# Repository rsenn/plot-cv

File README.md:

# EAGLE viewer (name pending — see below)

A browser-based viewer/editor for EAGLE CAD `.brd`/`.sch`/`.lbr` XML files: parses
the EAGLE XML DOM, renders schematics and boards to SVG, and drives a CAM pipeline
(Gerber export, G-code conversion) for board files. Includes a project/file chooser
for browsing available EAGLE projects on the backend.

Currently named "EAGLE renderer" (`index.html` `<title>`) — that name undersells the
CAM/editing features and needs to change. Candidates:

- **Eyrie** / **Aerie** — a bird of prey's nest; keeps the EAGLE association as a real
  English word instead of the acronym.
- **TalonView**
- **Wingspan**
- **BoardScope**
- **SchemaHawk**
- **CircuitEye**
- **GerberEye**

## Architecture

- **`index.html` + `main.js`** — the browser frontend. Preact-based UI (custom bundled
  `lib/preact.js`, not the npm package) that renders the SVG document, project/file
  chooser, layer controls, and CAM tooling. Talks to the backend over `fetch`/XHR
  (`commands.js`) and WebSockets (serial bridge, live update pushes).
- **`server.js`** — the current backend: a Node/Express server exposing the project's
  file listing, EAGLE file load/save, Gerber/G-code conversion, serial-port bridging
  (websocket), and static asset serving that `main.js` depends on.
- **`upload-server.js`** — an experimental, partial replacement backend built directly
  on qjs-net's low-level `createServer()` (QuickJS), meant to eventually take over from
  `server.js`. Not yet endpoint-compatible with `main.js`/`commands.js` — see `TODO.md`.

## OpenCV/ImGui Viewer

Simple OpenCV viewer using Dear ImGui interface.

Only testd on MacOSX.

# Dependency

- OpenCV>3.0
- SDL2
- Dear ImGui

# How to build

```
git clone https://github.com/ocornut/imgui.git
mkdir build
cd build
export OpenCV_DIR=OPENCV_INSTALL_PATH
cmake ..
make
```

# Root Script Index

Every `*.js` file directly in the repo root that has its own `main(...)` entry point
(`grep -lE '\bmain\s*\(' *.js`), sorted by line count as a rough proxy for
importance/complexity — substantial standalone tools/servers/apps at the top,
small one-off `test-*.js` smoke-test scripts at the bottom.

| Script | Lines | Description |
|---|---:|---|
| `tradeview.js` | 2166 | GLFW/nanovg GUI viewer for a crypto trading bot's SQLite database — renders candlestick charts, signals, trade brackets, and equity curve |
| `resolve-imports2.js` | 1730 | recursively resolves and concatenates a JS module's ES6 import graph into a single bundled `.es` output file |
| `eagle-shell.js` | 1657 | interactive REPL shell for loading EAGLE CAD schematic/board XML projects and manipulating parts, layers, and renderers, with gerber/gcode/SVG tools |
| `ast-shell.js` | 1655 | interactive REPL shell for compiling C/C++ sources to clang AST-dump JSON and exploring types/functions/structs, with FFI class generation |
| `resolve-imports.js` | 1397 | CLI ES-module tool that lexes JS files' import/export statements and can strip/rewrite imports, print dependency trees, or write reports |
| `upload-server.js` | 1328 | qjs-net HTTPS/WebSocket file-upload server — accepts multipart uploads, lists/serves them with directory browsing and thumbnails, plus a REPL |
| `fire.js` | 1019 | browser demo — renders a classic "Doom fire" pixel-propagation effect on canvas, seeded by mouse/touch input via a requestAnimationFrame loop |
| `debugger-server.js` | 1014 | qjs-lws WebSocket server that spawns and manages a QuickJS debugger session, relaying debugger protocol messages to connected clients |
| `server.js` | 947 | Express.js backend for the EAGLE/gerber CAD viewer web app — routes for gerber/gcode conversion, VFS/file access, serial ports, project save/config |
| `test-video.js` | 786 | interactive OpenCV.js video-processing test harness — reads a video/camera source through a Canny/contour/Hough pipeline with MIDI input |
| `test-opencv.js` | 723 | interactive OpenCV.js/GLFW smoke-test app — builds a live image-processing pipeline (threshold, Hough, skeleton) with mouse/keyboard tuning |
| `svg-crop-pad.js` | 682 | CLI that loads SVG files, computes/prints their bounding box, and rewrites the `viewBox`/width/height to crop or pad the drawing |
| `webakeit-telegram.js` | 633 | site-specific variant of the Telegram-export-to-blog converter, tailored to build `blog.html` for the webakeit bakery site |
| `dump-structs.js` | 592 | runs C/C++ source through `clang -ast-dump`, analyzes typedef'd structs/function prototypes, and generates JS ArrayBuffer struct/FFI bindings |
| `telegram-to-blog.js` | 569 | converts a Telegram Desktop HTML chat export into a self-contained static HTML blog page, copying/rotating referenced photos |
| `dump-ast.js` | 496 | runs `clang -ast-dump=json` on a C source file, then walks the AST to locate structs, printf-family calls, and format-string argument ranges |
| `test-xml.js` | 472 | reads a Sublime Text `.tmTheme` XML color scheme, extracts its color palette, applies a chosen transform, and writes back a modified theme |
| `list-exports.js` | 458 | lexes JS/BNF-family source files to find `import`/`export` statements and prints an `import { ... } from 'file'` summary line per file |
| `object_detection.js` | 451 | OpenCV.js DNN sample — loads a Caffe/TensorFlow/Darknet/ONNX model, runs object detection on video/camera/image with NMS |
| `create-tamper.js` | 437 | parses a set of JS module files, inlines/resolves their imports/exports recursively, and emits a bundled Tampermonkey userscript |
| `adsb-server.js` | 430 | qjs-lws WebSocket/TCP server that watches ADS-B state-dump files (inotify) and serves live aircraft-state updates to connected clients |
| `google-contacts.js` | 415 | QuickJS CLI that OAuth2-authenticates with Google People API, fetches all contacts, and prints/dumps them sorted by last-modified time |
| `photo_categorizer.js` | 412 | runs YOLOv8 (ONNX via OpenCV dnn) on all images in a folder, sorts each into a category subfolder based on detected objects |
| `test-rpc.js` | 410 | RPC/WebSocket test harness — starts an RPC client or server (file-serving, upload, proxy handlers) and drops into an interactive REPL |
| `test-image.js` | 404 | interactive OpenCV image viewer/pipeline tool — opens a window with mouse callback, runs images through an `ImagePipeline`, exports SVG/JSON |
| `eagle-server.js` | 376 | WS/HTTP backend server (custom `net` module) — serves static files plus `/config` and `/files` routes over TLS/WS, with a live-control REPL |
| `test-imgui.js` | 345 | interactive GLFW+nanovg+ImGui demo window exercising most ImGui widget bindings alongside a simple nanovg-drawn diamond shape |
| `ffi.js` | 327 | low-level libc FFI test/demo — dlopen/dlsym libc, calls malloc/strlen/strdup, then opens a raw TCP socket via syscalls and sends a manual HTTP GET |
| `test.js` | 314 | exercises OpenCV geometry/contour bindings plus edge/contour detection (Canny, findContours) on an input image, walking the contour hierarchy |
| `test-ffi.js` | 308 | exercises the custom `ffi` QuickJS module — dlopen/dlsym/call on libc functions, a bundled test.so, and inline x86-64 machine code |
| `test-parsetmpl.js` | 308 | tests `ECMAScriptParser`'s handling of tagged template literals, extracting tagged-template call nodes and running a JSX-string tokenizer |
| `list-proxies.js` | 303 | Node.js CLI that scrapes free proxy lists from multiple sources for given country codes, pings each proxy, and writes sorted results |
| `test-quickjs.js` | 299 | smoke test/exercise of the `opencv` module bindings (CV_* constants, Contour push/index/fitLine/fitEllipse), largely mirroring test-cv.js |
| `svg-box.js` | 292 | generates a laser-cutter SVG template for a box (lid/bottom/front/back/sides) with measurement annotations from CLI dimension args |
| `yolo.js` | 287 | real YOLOv3 object-detection CLI using OpenCV `dnn` — runs inference on image/video/webcam, draws bounding boxes+labels, saves JSON detections |
| `test-ecmascript2.js` | 284 | near-duplicate of test-ecmascript.js — parses a JS file, writes AST JSON and reprinted source, reporting parse success/failure |
| `test-eagle.js` | 278 | exercises the `lib/eagle.js` EAGLE CAD project API — loads a board/schematic project, normalizes pads, aligns elements to grid, saves documents |
| `test-mmap.js` | 275 | binary-patching tool — mmaps a target executable, scans it for byte patterns (license-check signatures), and writes out a patched copy |
| `blackbody.js` | 263 | looks up an RGB gamma correction triple for a given color temperature in a blackbody color table and prints an mpv/ffmpeg filter string |
| `doc-scanner.js` | 256 | OpenCV document-scanner script — finds the largest 4-point contour in an image, warps/crops it to a fixed page size, displays/writes results |
| `list-exports2.js` | 256 | CLI that parses a JS file, extracts its exported/imported identifiers, and prints/writes a synthesized `import {...} from './file'` statement |
| `test-nanovg.js` | 251 | interactive GLFW+nanovg+ImGui+OpenCV demo — draws a background image, animates transformed shapes with nanovg, renders an ImGui panel |
| `clang-list.js` | 249 | CLI that runs/loads a clang AST dump for given source files (caching), flattens it, and prints a table of named declarations |
| `test-ecmascript.js` | 248 | CLI that parses a JS file (or stdin) with the custom `ECMAScriptParser`, dumps the AST to JSON, and reports imports/requires/templates |
| `test-kolorwheel.js` | 238 | generates/prints color palettes/gradients using `KolorWheel`/`HSLA`/`RGBA`, mapping Eagle CAD layer names to a randomized palette |
| `test-cv.js` | 230 | smoke test of the `opencv` module bindings — Rect/Point/Size/Line/Mat/Contour constructors, Mat pixel get/set, iterators |
| `get-msys-packages.js` | 227 | downloads MSYS2/MinGW package DB files, resolves package/dependency args against them, and generates a script to curl+extract matches |
| `svgtransform.js` | 222 | CLI that reads an SVG/XML file, applies accumulated `transform` attributes as matrices to child elements, and rewrites their coordinates |
| `test-tmtheme.js` | 221 | converts TextMate `.tmLanguage`/`.tmTheme` plist XML files to/from a JS object model, extracts scope names, and rewrites the plist file |
| `cv-shell.js` | 213 | interactive OpenCV/CV REPL shell wiring up image/video helpers, history, and globals for live experimentation with `qjs-opencv` |
| `svg-scale.js` | 213 | CLI that reads SVG file(s), inlines CSS classes into attributes, reformats path data, and resizes the SVG to a given size, rewriting in place |
| `gerber2gcode.js` | 208 | CLI that groups Gerber/drill files by board, parses them, builds a `pcb2gcode` command line, runs it, and post-processes the resulting SVG |
| `scan.js` | 197 | OpenCV-based A4 document scanner CLI: detects the page quadrilateral, perspective-warps/thresholds it, and writes contour JSON plus PNG outputs |
| `check-discogs.js` | 196 | fetches Discogs seller order pages via spawned `curl` for given order IDs and prints/collects order info (mostly a stub) |
| `esparse.js` | 195 | CLI that parses a JS source file with the custom `ECMAScriptParser`, adds comments to the AST, and writes it as JSON to an output file |
| `compile_commands.js` | 194 | loads a `compile_commands.json`, builds `CompileCommand` objects and dependency maps, and parses CMake `link.txt` files |
| `test-ecmascript3.js` | 193 | CLI driver for the project's custom ECMAScript parser: parses input file(s), pretty-prints the AST back to `.es`/`.ast.json`, scans imports |
| `test-bjson.js` | 177 | standalone test of a custom `bjson.so` binary-JSON module — round-trips a BJSON file to JSON, with zlib/XML FFI helpers defined but unused in main() |
| `test-ini.js` | 175 | parses a `.desktop`/INI-style file with a custom INI grammar and converts it into an icon entry or reshuffles sections, rewriting the file |
| `test-umat.js` | 175 | OpenCV demo dumping Mat type constants, then running Canny/Hough/contour analysis on a schematic image and displaying results |
| `xml2js.js` | 172 | CLI that reads an XML file (e.g. EAGLE board file), converts it to a `Tree`, strips empty/wrapper nodes, and writes cleaned JSON/BJSON/XML |
| `test-filesystem.js` | 164 | TinyTest-based unit test suite exercising the `filesystem` module's buffer/file/dir API against a temp directory |
| `test-debuggerprotocol.js` | 159 | CLI that opens a raw TCP socket to a QuickJS debugger endpoint (client or server mode) and drives the `DebuggerProtocol` class |
| `adsb-client.js` | 157 | polls the OpenSky Network REST API for ADS-B aircraft state vectors every 10s and appends the JSON responses to rotating log files |
| `test-imread.js` | 156 | OpenCV demo that loads a bitmap-font image, segments it into a character grid, renders each glyph as ASCII art in a GUI window |
| `test-membrane.js` | 153 | parses an EAGLE `.brd` XML file, exercising the `deep`/`ImmutablePath`/`XMLIterator`/`ImmutableXPath` membrane-style path-mapping APIs |
| `sky_detect.js` | 149 | OpenCV CLI tool that loads an image, builds an HSV-based sky mask, finds the largest contour, and writes mask/contour PNG outputs |
| `test-midi.js` | 149 | standalone smoke test connecting to a TCP MIDI stream, decoding incoming bytes into MIDI events and logging them |
| `search-engine.js` | 147 | async scraper that queries several search-engine URL templates, parses HTML with the custom DOM parser, and extracts `src`/`href` links |
| `test-cparse.js` | 144 | exercises the custom `cpp`/`cparse` C preprocessor and parser libraries by preprocessing/parsing a hardcoded quickjs C source file |
| `test-minnet.js` | 143 | smoke test/demo of the `net` (minnet) module's `createServer`/`client`/`fetch` APIs, selectable via CLI arg |
| `convert-imports.js` | 142 | CLI that parses a JS file, finds `require()`/`import` nodes via `deep.select`, and converts between `import` and `require` styles |
| `test-glfw.js` | 138 | opens a GLFW/OpenGL window, loads image(s) via `opencv.imread`, uploads them as GL textures, and animates a color-cycling textured quad |
| `midi-tcp.js` | 130 | connects to a TCP MIDI stream, parses incoming MIDI events with `MIDIStream`/`MIDIEvent`, and reads raw stdin bytes (Ctrl-D to quit) |
| `eagle2gerber.js` | 129 | CLI tool that invokes the Eagle CAD binary to export Gerber/Excellon layers from `.brd` files, then zips the generated output folder |
| `test-features2d.js` | 119 | iterates OpenCV's Feature2D detector/descriptor classes (ORB, AKAZE, SURF, MSER, etc.), computes keypoints, and displays them |
| `test-fft.js` | 109 | loads a WAV file via `libsndfile` (raw FFI), runs an FFT (`lib/dsp/fft.js`) on a windowed segment, and prints the dominant frequency bin(s) |
| `yt-playlist.js` | 98 | runs `yt-dlp` as a subprocess to fetch JSON metadata for a YouTube playlist URL, then writes the collected results to `out.json` |
| `test-attributes.js` | 97 | reads XML files, collects the set of attribute names used per tag across all elements, and prints which attribute names hold numeric values |
| `bs.to-serie.js` | 96 | scrapes a "Burning Series" streaming site — reads show URLs from a text file and extracts metadata (title, actors, genres, years) into an array |
| `test-net.js` | 93 | smoke-test of the `net.so` module's `fetch()` — performs a GET request to google.com with a custom User-Agent |
| `xml2react.js` | 93 | reads XML (from a file or stdin) and converts it into `h(...)`-style React/hyperscript-like JS source code, printed to stdout |
| `read-deps.js` | 90 | runs `g++ -MM` to compute header dependencies for C/C++ sources, writes `deps.mk`, and cross-checks against a manual `#include` scan |
| `test-proxy.js` | 89 | reads an Eagle `.brd` XML file, wraps it in a lazy `Proxy`-based node/nodelist tree, and walks it with `deep.select` to find named parts |
| `extract-structs.js` | 87 | lexes a C source file with `CLexer` and prints out top-level `struct`/`typedef` declarations found at column 1 |
| `make-bitmap.js` | 87 | interactive OpenCV pipeline tool that loads an image, applies grayscale + adjustable threshold via a trackbar, and displays the result |
| `test-coverage.js` | 86 | reads a V8 coverage JSON report, matches script URLs against a regex, and computes/extracts used vs. unused source code ranges |
| `count-neighbours.js` | 85 | loads an image, thresholds/skeletonizes it with OpenCV, computes pixel-neighborhood/skeleton tracing, and drops into an interactive REPL |
| `test-inspect.js` | 82 | smoke-tests the QuickJS `inspect`/`Console` utilities by building an object with exotic values and printing it with various inspect options |
| `test-jsjs.js` | 82 | parses JS source file(s) with the custom `ECMAScriptParser`, re-prints the AST via `Printer` to a `.es` output file |
| `video-image-similarity.js` | 82 | opens a video file in an OpenCV `Window`, computes frame-to-frame MSE similarity in grayscale, and lets the user save frames as PNG |
| `ftrace.js` | 81 | parses an strace log file, reconstructs resumed syscalls, and writes lists of referenced filenames and functions that touched files |
| `test-childprocess.js` | 81 | spawns `ls -la` via `child_process.spawn`, sends SIGSTOP/SIGCONT to it, and streams its stdout via a custom `Repeater`-based reader |
| `eagle-query.js` | 80 | loads Eagle `.brd` board files, extracts R/C/L component values, builds value histograms, and prints a formatted report with color-code bands |
| `mailcow-db.js` | 79 | connects to a mailcow MySQL database (hardcoded host/credentials) and runs a test `SELECT * FROM mailbox` query |
| `test-cpp.js` | 76 | runs the local `lib/cpp.js` C preprocessor against a source file (invoking `cc1 -E` for reference), printing the expanded output |
| `splitdiff.js` | 75 | CLI tool that parses unified diff files and splits each hunk/chunk into its own `.diff` file, optionally skipping whitespace-only chunks |
| `test-geda-netlist.js` | 74 | parses gEDA netlist files, extracts components/nets, and writes each as a formatted JSON file |
| `test-diagram.js` | 73 | uses the local `diagram.js` axis/plotting helpers with `opencv` to draw a chart onto a Mat, saving `diagram.png` |
| `test-geom.js` | 73 | smoke-tests the `lib/geom.js` Point/PointList/Matrix API — rotate, centroid, bbox, area, transform, etc. |
| `test-websocket.js` | 73 | connects to a local `ws://127.0.0.1:3000/ws` server, sends a PING message, and handles HELLO/PONG/USERS/INFO/QUIT protocol messages |
| `test-renderer.js` | 69 | renders Eagle CAD schematic/board files for given basenames via `EagleDocument`/`Renderer`/Preact, writing SVGs to `tmp/*.svg` |
| `httpd.js` | 68 | spawns an `os.Worker` running `./ws-worker.js`, forwards `--host`/`--port` options to it, and relays messages (simple HTTP/WebSocket server driver) |
| `images2video.js` | 68 | CLI (opencv) that resizes/pads a list of images to a fixed canvas and encodes them into an MP4 via `VideoWriter` |
| `test-meriyah.js` | 68 | CLI that parses JS files via the npm `meriyah` package's `parseScript` and writes each file's AST as `<name>.ast.json` |
| `test-parse.js` | 68 | loads a grammar file into the custom `Grammar` parser, generates a JS parser module, and runs its `selector` against a sample string |
| `test-esprima.js` | 67 | CLI that parses JS files via the local `esprima` module's `parseModule` and writes each file's AST as `<name>.ast.json` |
| `test-console.js` | 66 | exercises the `console`/`inspect` implementation's formatting of functions, bound functions, Maps, WeakMaps, and null-prototype objects |
| `test-jslexer.js` | 66 | lexes a given file (default `./lib/misc.js`) using `lib/jslexer.js`, printing each token's id/lexeme/location |
| `test-utf8.js` | 65 | reads a file's raw bytes and decodes UTF-8 byte sequences into code points/strings using both a generator and a reduce-based decoder |
| `eagle2svg.js` | 64 | CLI that opens Eagle CAD files (schematic/board/library), renders them via `EagleDocument`/`Renderer` to SVG, and writes `<name>-<type>.svg` files |
| `bjson.js` | 63 | CLI that converts files between JSON and the binary `bjson.so` format based on `getOpt` args |
| `test-debug.js` | 63 | connects a `SocketDebugClient` (Debug Adapter Protocol) to a debug adapter on localhost:6666, sets breakpoints, and listens for stop events |
| `test-shparse.js` | 63 | spawns/reads a shell-parser AST via external `shparse2ast` (or a `.json` file), then parses and logs it |
| `meriyah.js` | 59 | CLI that parses a JS file with the local `meriyah` parser and writes the resulting AST as JSON to stdout or a file |
| `test-tree.js` | 59 | exercises the `Tree` wrapper class over a nested sample object, testing entries/indexOf/keyOf/pathOf/push/shift/flat/remove APIs |
| `test-lexer.js` | 57 | lexes a given file (default `./lib/ecmascript/parser.js`) with the custom ECMAScript `Lexer`, printing each token colorized by type |
| `test-eval.js` | 53 | parses a hardcoded JS snippet with the custom `ECMAScriptParser`, evaluates its AST in a sandboxed `Environment`, and writes reprinted source |
| `test-util.js` | 50 | exercises the local `Util` helper module (trace, getPlatform, waitFor, now, isAsync) and basic `filesystem` file writing |
| `test-octagon.js` | 46 | generates octagon/10-gon polygons via `MakePolygon`, builds SVG paths with `SvgPath`, and writes the composed SVG to `output.svg` |
| `test-cli.js` | 45 | smoke-tests the `opencv` binding's geometry/draw classes (Point, Size, Rect, Contour, Line, Draw) by constructing and iterating them |
| `test-lex.js` | 43 | runs the custom ECMAScript `Lexer` over input file(s) (or stdin), lexing all tokens and recording per-file errors |
| `test-ngql.js` | 41 | builds a GraphQL query with `nanographql`, POSTs it to a hardcoded Heroku GraphQL endpoint, and logs the JSON response |
| `test-pointer.js` | 39 | exercises the `pointer`/`deep` native modules — builds a `Pointer`, uses `deep.set` to write into an object via the pointer path |
| `test-gpio.js` | 38 | smoke-tests the native `gpio` module by initializing output/input pins, setting/reading a pin, and dumping the GPIO mmap buffer |
| `test-description.js` | 37 | reads Eagle CAD XML files given as args and extracts/prints the `<description>` text found in the board/schematic/library element |
| `test-sockets.js` | 36 | opens an `AsyncSocket` (AF_INET/TCP), connects to a hardcoded host on port 22, asynchronously receives data, and logs the escaped response |
| `test-circuit.js` | 34 | parses an electronics `.circuit` file with `CircuitFileParser`, logs its elements, then re-serializes it with `CircuitFileWriter` |
| `fontsample.js` | 33 | builds a byte array covering all 256 char codes as a font sample, logs it, and writes the string form to `output.txt` |
| `test-archive.js` | 31 | opens a tar.xz archive via the `archive` module, iterates/extracts its entries, and logs progress and file count |
| `test-readline.js` | 31 | reads a single line of input via the local `readline.js` module's `readline()` at a prompt |
| `takephoto.js` | 30 | uses the `opencv` binding's `RaspiCam` to capture a photo at 2592x1944 and saves it to `photo.png` |
| `test-repl.js` | 29 | starts an interactive `REPL` (from `./repl.js`) with mouse tracking enabled via the `Terminal` module, adding a custom compile directive |
| `test-io.js` | 28 | implements an async `FileReader` using `filesystem` + `Repeater` and streams its own source in 64-byte chunks to the console |
| `test-call.js` | 27 | defines a `Callable` class extending `Function` and tests constructing it both from a JS function and from `(args, body)` strings |
| `test-css3.js` | 27 | runs the `grammar-css3.js` `selector` parser against a hard-coded complex CSS selector string, reporting SUCCESS/FAIL |
| `test-path.js` | 26 | exercises the local `lib/path.js` module's API (basename, relative, sep, delimiter, etc.) against the current script path |
| `test-clexer.js` | 25 | reads a C source file (default `pa_devs.c`) and tokenizes it with the `tokenize` module, logging each token |
| `test-stack.js` | 24 | logs a custom-inspected object and exercises `Util.getStackFrame`/`Util.getCallerStack` to print current call-stack info |
| `fetch-post-prices.js` | 22 | spawns `curl` via `os.exec`/pipes to fetch the Swiss Post pricing info page and prints the raw HTML/JSON response |
| `test-readdir.js` | 22 | recursively lists `.c`/`.h` files under `.` using `ReadDirRecursive`/a filter generator, then sends itself `SIGUSR1` |
| `test-containers.js` | 21 | exercises `MultiKeyMap`, `MultiBiMap`, and `HashMultimap` container classes by inserting sample entries and logging their contents/keys/values |
| `test-sourcemap.js` | 21 | builds `SourceMap` objects from `//# sourceMappingURL=` comments for htm/preact map files and logs their base64 and comment forms |
| `test-editline.js` | 20 | uses `ffi` to `dlsym` the `rl_meta_chars` symbol from the loaded `editline` library handle and dumps it as a hex address and ArrayBuffer |
| `test-bash-parser.js` | 19 | reads `../cfg.sh` and parses it with the `bash-parser` module, logging the resulting AST |
| `test-import.js` | 17 | imports the `bjson` module and dynamically imports `ffi`, logging both to check they load correctly |
| `test-parsexml.js` | 17 | reads an XML file, parses it with `lib/xml/parse.js`, and re-serializes the result back to XML via `lib/json.js`'s `toXML` |
| `test-linenoise.js` | 15 | loads/saves history and runs an interactive `linenoise` prompt loop, echoing each entered line until `quit` |
| `test-psql.js` | 14 | uses the local `psql.js` FFI wrapper to open a libpq connection to a local Postgres DB, run `SELECT * FROM test`, and log the result/error |
| `test-exception.js` | 13 | logs its args then unconditionally throws an `Error('This is an error')` to exercise error/exception handling |
| `test-sqlite3.js` | 10 | calls `sqlite3_open` from the local sqlite3 FFI binding to open a Chrome `History` sqlite file and logs the return code |
| `test-stream.js` | 9 | opens `tmp/7seg-2.54.brd` via the `filesystem` module, reads it async, and opens `tmp/test.txt` for writing (result unused) |

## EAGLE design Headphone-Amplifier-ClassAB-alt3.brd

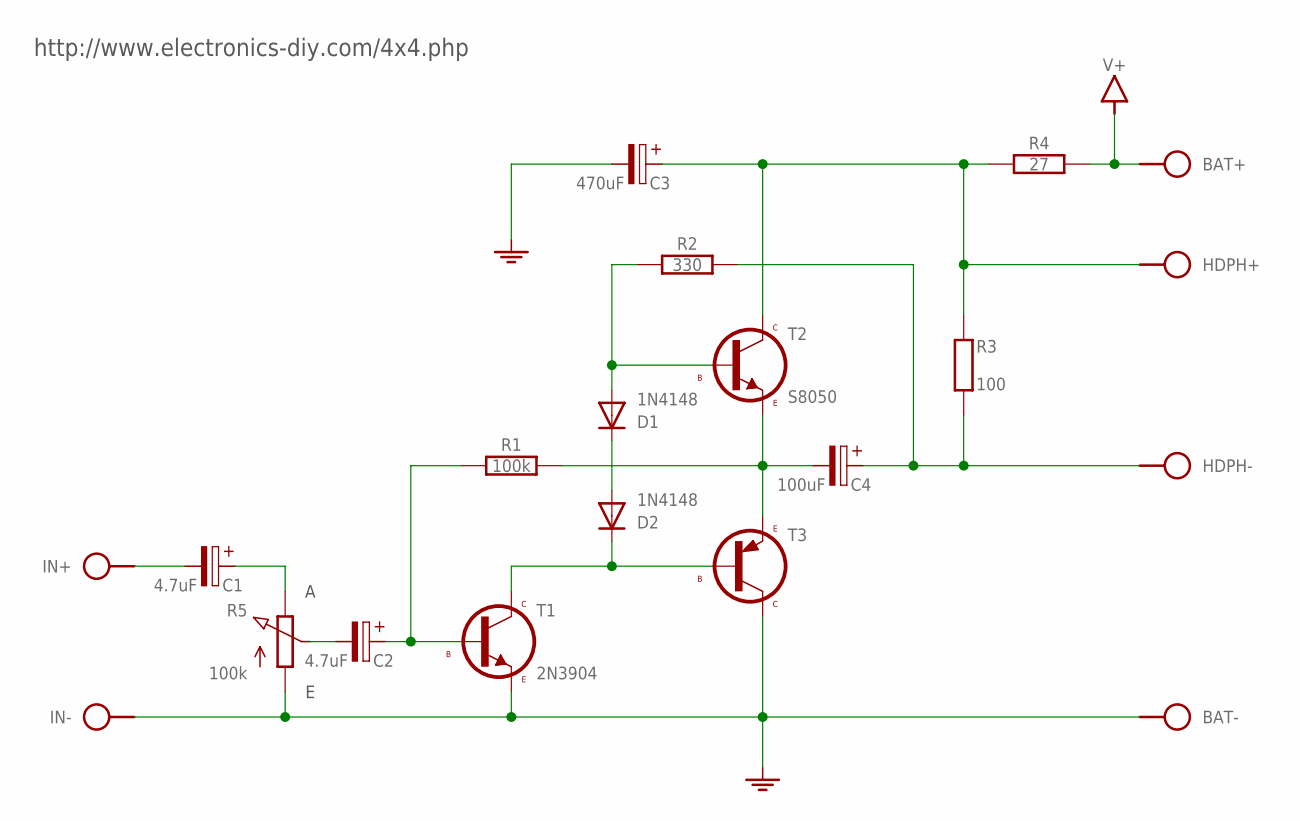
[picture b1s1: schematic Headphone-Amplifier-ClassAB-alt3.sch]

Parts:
BAT: SPAD+-+-; SPAD+-
C1, C2: 4.7uF; E2,5-3
C3: 470uF; E2,5-5/V
C4: 100uF; E5-4
D1: 1N4148; DO34-5-V
D2: 1N4148; DO34-5V
HDPH: SPAD+--+; SPAD-+
IN: SPAD+--+; SPAD-+
R1: 100k; 0204/10
R2: 330; 0204/10
R3: 100; 0204/10
R4: 27; 0204/10
R5: 100k; CONN-3P
T1: 2N3904; TO92
T2: S8050; TO92
T3: S8550; TO92

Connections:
GND: BAT.1, C3.-, IN.1, R5.1 (A), T1.1 (E), T3.3 (C)
unnamed: D1.A, R2.1, T2.2 (B)
unnamed: D2.C, T1.3 (C), T3.2 (B)
unnamed: D1.C, D2.A
unnamed: C4.-, R1.2, T2.1 (E), T3.1 (E)
unnamed: C1.+, R5.3 (E)
unnamed: C2.-, R5.2 (S)
unnamed: C2.+, R1.1, T1.2 (B)
unnamed: C3.+, HDPH.2, R3.1 (2), R4.1, T2.3 (C)
unnamed: C4.+, HDPH.1, R2.2, R3.2 (1)
unnamed: C1.-, IN.2
V+: BAT.2, R4.2

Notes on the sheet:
http://www.electronics-diy.com/4x4.php

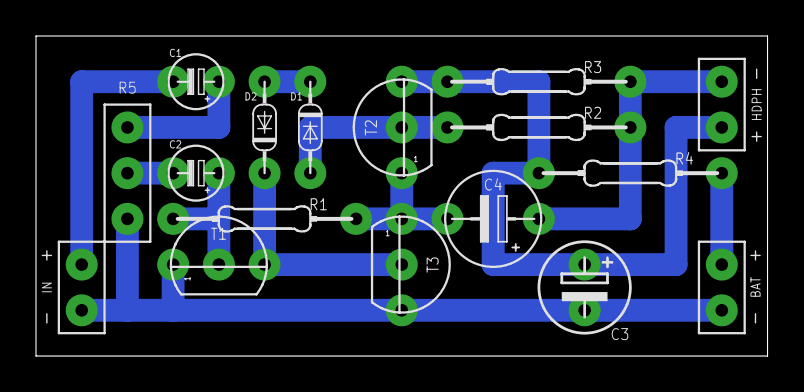
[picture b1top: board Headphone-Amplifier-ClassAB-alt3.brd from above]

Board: 2 copper layers, 40.6 x 17.8 mm, 17 parts (0 on the bottom side), 12 nets.

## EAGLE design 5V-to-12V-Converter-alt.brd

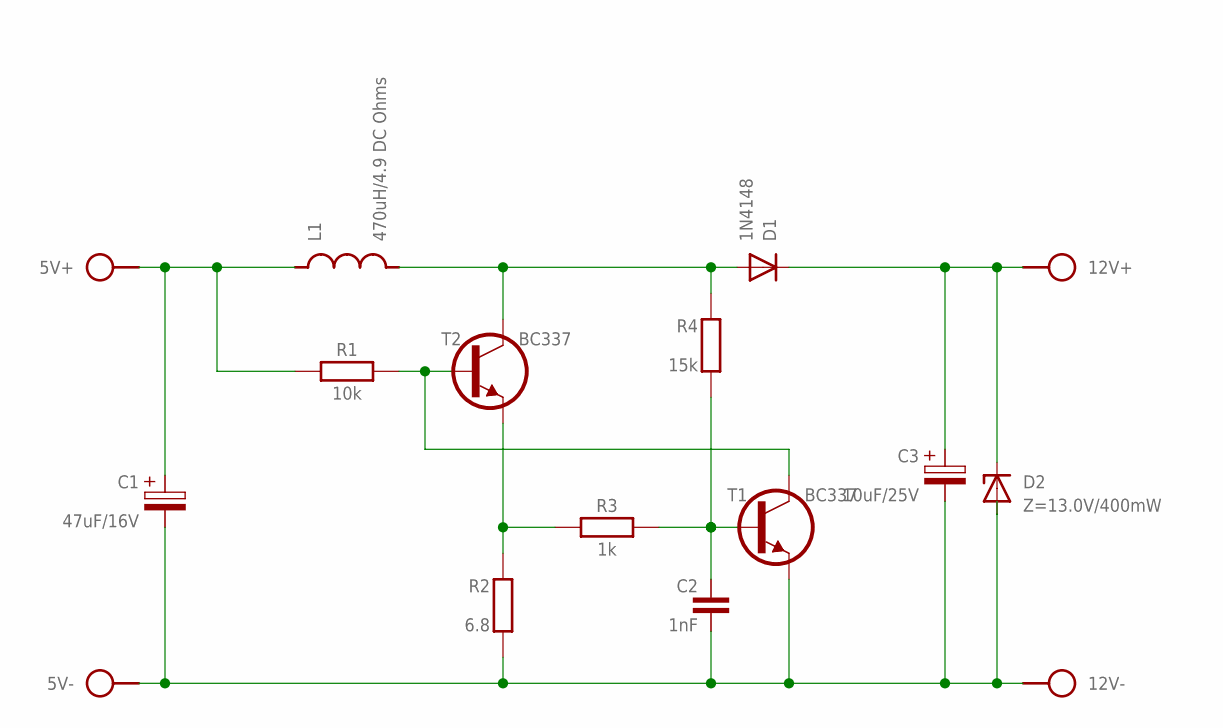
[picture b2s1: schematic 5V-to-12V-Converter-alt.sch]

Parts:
5V, 12V: SPAD+--+; SPAD-+
C1: 47uF/16V; E2.5-4/V
C2: 1nF; C050-020X036
C3: 10uF/25V; E2.5-4/V
D1: 1N4148; DO35-2_54A
D2: Z=13.0V/400mW; DO34Z12V
L1: 470uH/4.9 DC Ohms; ED16-X
R1: 10k; 0204/10
R2: 6.8; 0204/10
R3: 1k; 0204/10
R4: 15k; 0204/10
T1, T2: BC337; TO92-CBE

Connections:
GND: 5V.1, 12V.1, C1.-, C2.2, C3.-, D2.A, R2.1 (2), T1.E
unnamed: 12V.2, C3.+, D1.C, D2.C
unnamed: R2.2 (1), R3.1, T2.E
unnamed: C2.1, R3.2, R4.1 (2), T1.B
unnamed: R1.2, T1.C, T2.B
unnamed: 5V.2, C1.+, D1.A, L1.1, L1.2, R1.1, R4.2 (1), T2.C

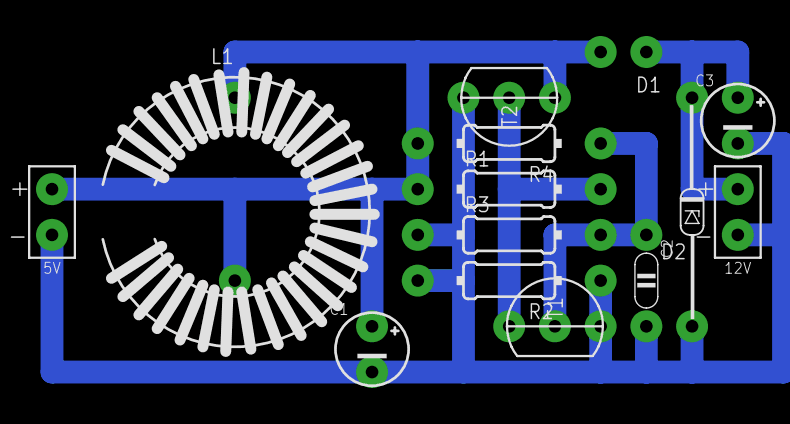
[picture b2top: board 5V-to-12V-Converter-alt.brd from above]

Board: 2 copper layers, 14 parts (0 on the bottom side), 6 nets.

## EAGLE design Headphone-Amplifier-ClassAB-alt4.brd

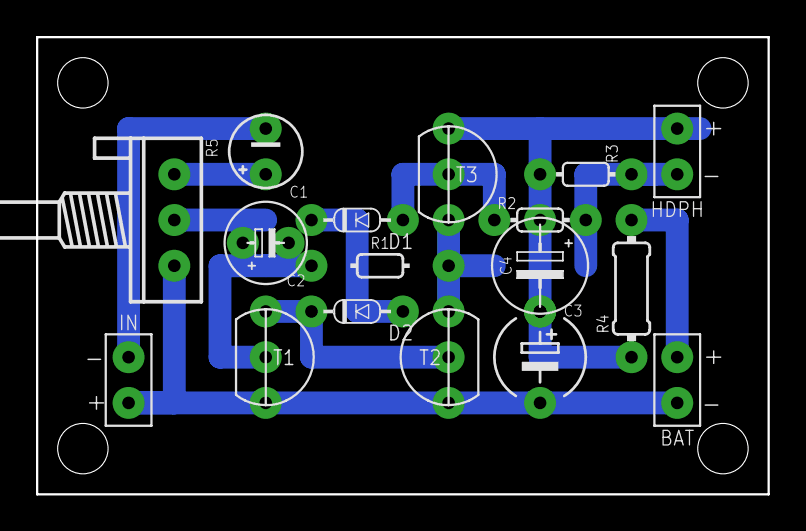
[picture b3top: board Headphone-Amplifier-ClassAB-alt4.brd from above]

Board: 2 copper layers, 40.6 x 25.4 mm, 17 parts (0 on the bottom side), 12 nets.

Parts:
BAT: SPAD+-+-; SPAD+-
C1: 4.7uF; E2.5-4/V
C2: 4.7uF; E2,5-4
C3: 100-1000uF; E5-5/V
C4: 220uF; E5-4
D1, D2: 1N4148; DO34-5
HDPH: SPAD+-+-; SPAD+-
IN: SPAD+-+-; SPAD+-
R1: 100k; 0202/7
R2: 330; 0202/5
R3: 100; 0202/5-V
R4: 22; 0204/7
R5: 100k; POT
T1, T3: BC547; TO92-CBE
T2: BC557; TO92-CBE

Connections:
GND: BAT.1, C3.-, IN.2, R5.E, T1.E, T2.C
unnamed: D1.A, R2.1, T3.B
unnamed: D2.C, T1.C, T2.B
unnamed: D1.C, D2.A
unnamed: C4.-, R1.2, T2.E, T3.E
unnamed: C1.+, R5.A
unnamed: C2.-, R5.S
unnamed: C2.+, R1.1, T1.B
unnamed: C3.+, HDPH.2, R3.2, R4.1, T3.C
unnamed: C4.+, HDPH.1, R2.2, R3.1
unnamed: C1.-, IN.1
V+: BAT.2, R4.2

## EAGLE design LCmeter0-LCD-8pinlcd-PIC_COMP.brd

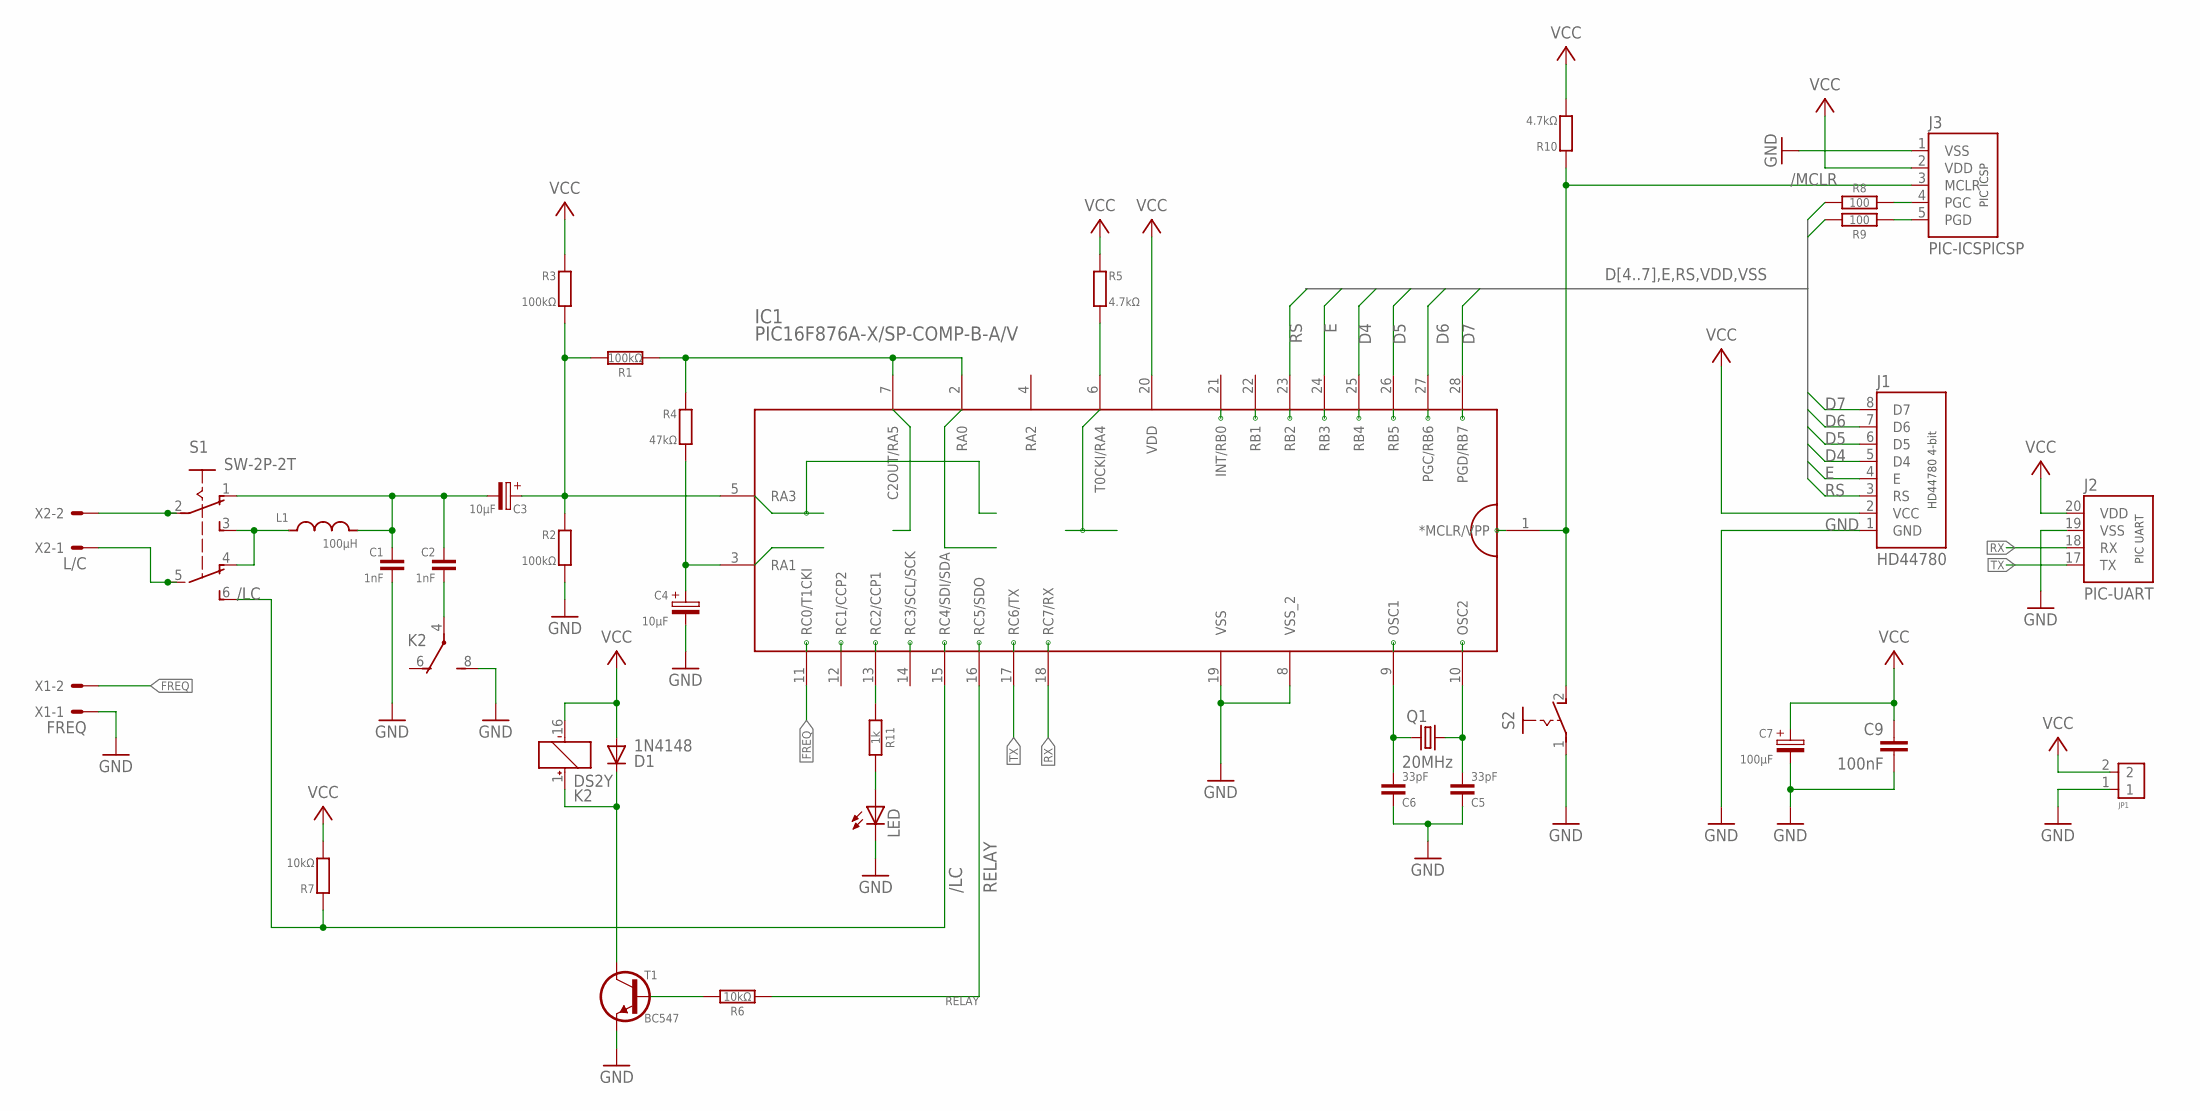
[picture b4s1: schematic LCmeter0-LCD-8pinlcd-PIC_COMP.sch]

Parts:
C1, C2: 1nF; C050-020X036
C3, C4: 10μF; E2,5-4
C5, C6: 33pF; C025-020X036
C7: 100μF; E2,5-5
C9: 100nF; C025-024X044
D1: 1N4148; DO34-7
IC1: PIC16F876A-X/SP-COMP-B-A/V; DIL28-3/V
J1: HD44780; CONN-8P
J2: PIC-UART
J3: PIC-ICSPICSP; PIC-ICSP
JP1: CONN-2P2P/V; CONN-2P-V
K2: DS2Y
L1: 100µH; L-02/5V
LED: TLLG4400; LED3MM
Q1: 20MHz; HC49
R1, R2, R3: 100kΩ; 0202/7
R4: 47kΩ; 0202/7
R5, R10: 4.7kΩ; 0202/7
R6: 10kΩ; 0202/7
R7: 10kΩ; 0202/10
R8, R9: 100; 0202/5
R11: 1k; 0202/5
S1: SW-2P-2T; SLSW-2P2T
S2: PB-1P-1T; PB-1P1T
T1: BC547; TO92-CBE-A
X1: FREQ; 70543-02
X2: L/C; 70543-02

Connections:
/LC: IC1.15 (RC4/SDI/SDA), R7.1, S1.6 (S1)
/MCLR: IC1.1 (*MCLR/VPP), J3.3 (MCLR), R10.1, S2.2 (S)
/RELAY: D1.C, K2.1 (+), T1.C
A0: IC1.2 (RA0), IC1.7 (C2OUT/RA5), R1.1, R4.1
A1: C4.+, IC1.3 (RA1), R4.2
A3: C3.+, IC1.5 (RA3), R1.2, R2.1, R3.2
A4: IC1.6 (T0CKI/RA4), R5.2
C2_CON: C2.2, K2.4
D4: IC1.25 (RB4), J1.5 (D4)
D5: IC1.26 (RB5), J1.6 (D5)
D6: IC1.27 (PGC/RB6), J1.7 (D6), R9.1
D7: IC1.28 (PGD/RB7), J1.8 (D7), R8.1
E: IC1.24 (RB3), J1.4 (E)
FREQ: IC1.11 (RC0/T1CKI), X1.2
GND: C1.2, C4.-, C5.1, C6.1, C7.-, C9.2, IC1.8 (VSS_2), IC1.19 (VSS), J1.1 (GND), J2.19 (VSS), J3.1 (VSS), JP1.1, K2.8 (S), LED.K (C), R2.2, S2.1, T1.E, X1.1
M+: S1.2, X2.2
M-: S1.5 (P1), X2.1
unnamed: J3.4 (PGC), R8.2
unnamed: C1.1, C2.1, C3.-, L1.2, S1.1 (O)
unnamed: J3.5 (PGD), R9.2
unnamed: IC1.13 (RC2/CCP1), R11.2
unnamed: R6.1, T1.B
unnamed: LED.A, R11.1
unnamed: L1.1, S1.3 (S), S1.4 (O1)
OSC1: C6.2, IC1.9 (OSC1), Q1.1
OSC2: C5.2, IC1.10 (OSC2), Q1.2
RELAY: IC1.16 (RC5/SDO), R6.2
RS: IC1.23 (RB2), J1.3 (RS)
RX: IC1.18 (RC7/RX), J2.18 (RX)
TX: IC1.17 (RC6/TX), J2.17 (TX)
VCC: C7.+, C9.1, D1.A, IC1.20 (VDD), J1.2 (VCC), J2.20 (VDD), J3.2 (VDD), JP1.2, K2.16 (-), R3.1, R5.1, R7.2, R10.2

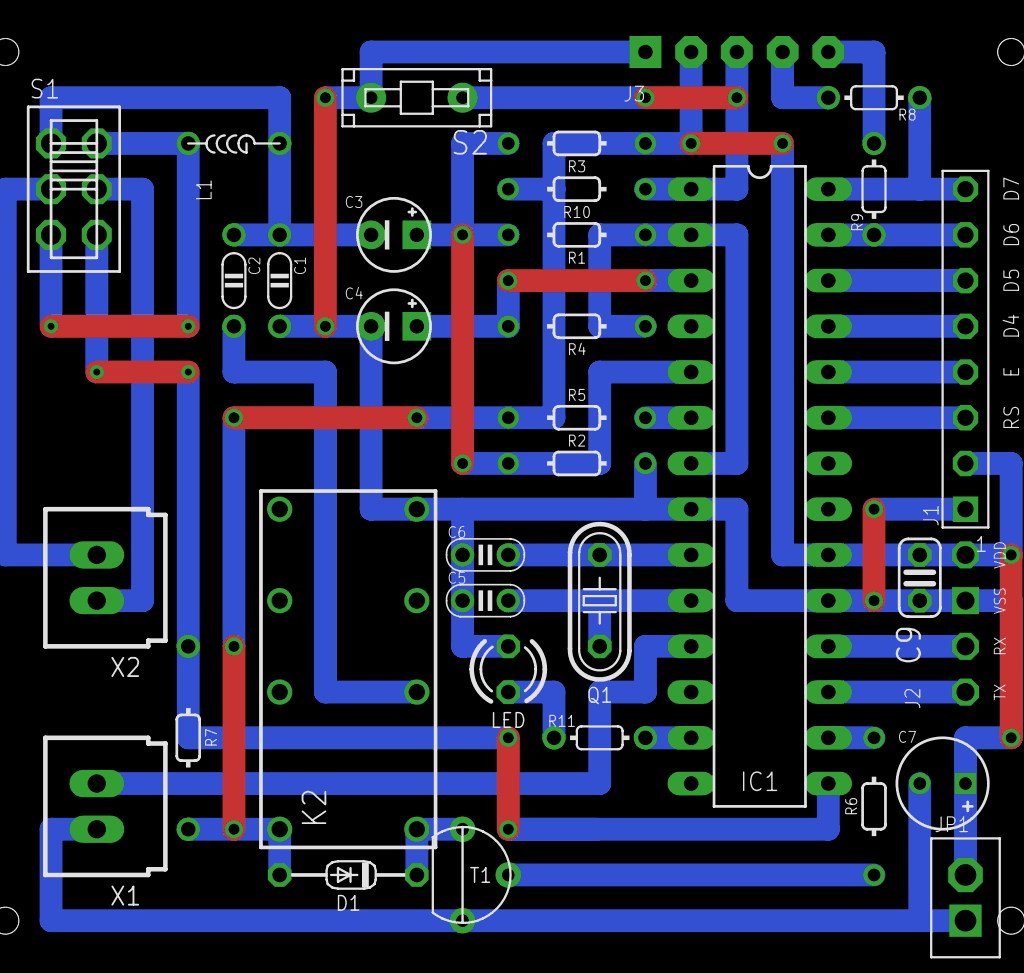
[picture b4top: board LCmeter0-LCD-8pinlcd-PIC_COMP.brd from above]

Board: 2 copper layers, 34 parts (0 on the bottom side), 31 nets.

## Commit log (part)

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2026-05-12 translated coinbase-bot.py
